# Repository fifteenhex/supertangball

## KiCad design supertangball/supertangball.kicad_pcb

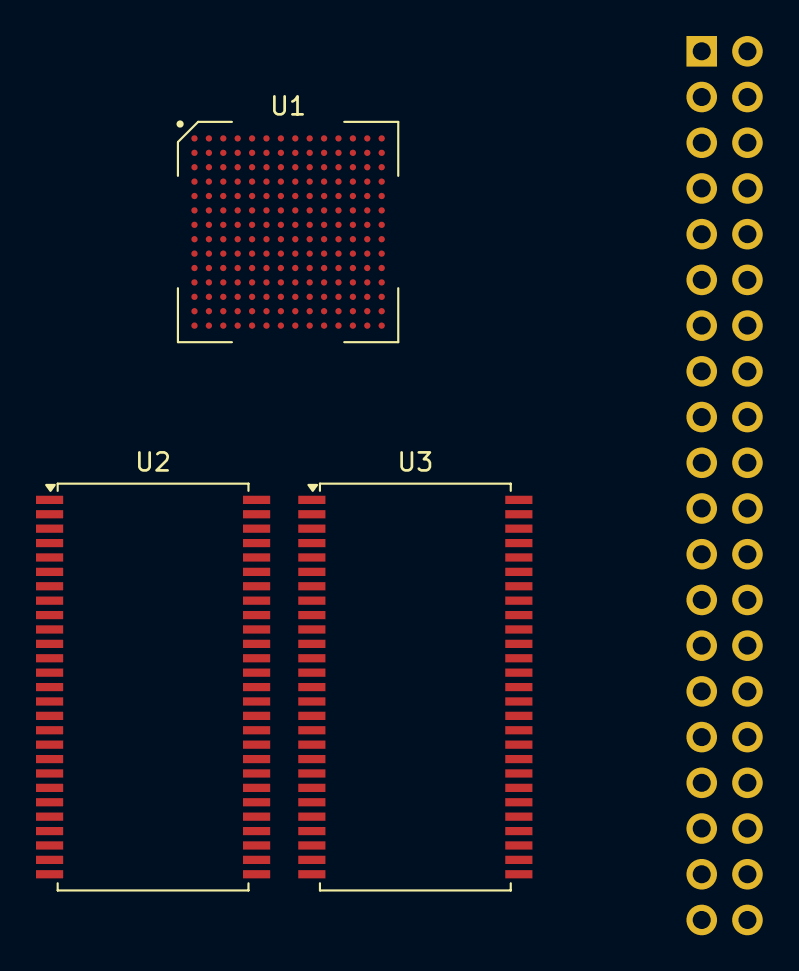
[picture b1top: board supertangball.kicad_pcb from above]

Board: 2 copper layers, 4 parts (1 on the bottom side), 8 nets, no tracks yet.

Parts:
J1: Conn_02x20_Odd_Even; PinSocket_2x20_P2.54mm_Vertical
U1: BGA-196_14x14_12.0x12.0mm
U2, U3: MT48LC16M16A2TG; TSOP-II-54_22.2x10.16mm_P0.8mm

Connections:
unnamed: U2.1 (VDD), U2.14 (VDD), U2.27 (VDD)
unnamed: U2.3 (VDDQ), U2.9 (VDDQ), U2.43 (VDDQ), U2.49 (VDDQ)
unnamed: U2.28 (VSS), U2.41 (VSS), U2.54 (VSS)
unnamed: U2.6 (VSSQ), U2.12 (VSSQ), U2.46 (VSSQ), U2.52 (VSSQ)
unnamed: U3.1 (VDD), U3.14 (VDD), U3.27 (VDD)
unnamed: U3.3 (VDDQ), U3.9 (VDDQ), U3.43 (VDDQ), U3.49 (VDDQ)
unnamed: U3.28 (VSS), U3.41 (VSS), U3.54 (VSS)
unnamed: U3.6 (VSSQ), U3.12 (VSSQ), U3.46 (VSSQ), U3.52 (VSSQ)

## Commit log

2024-03-20 soo many pins!
